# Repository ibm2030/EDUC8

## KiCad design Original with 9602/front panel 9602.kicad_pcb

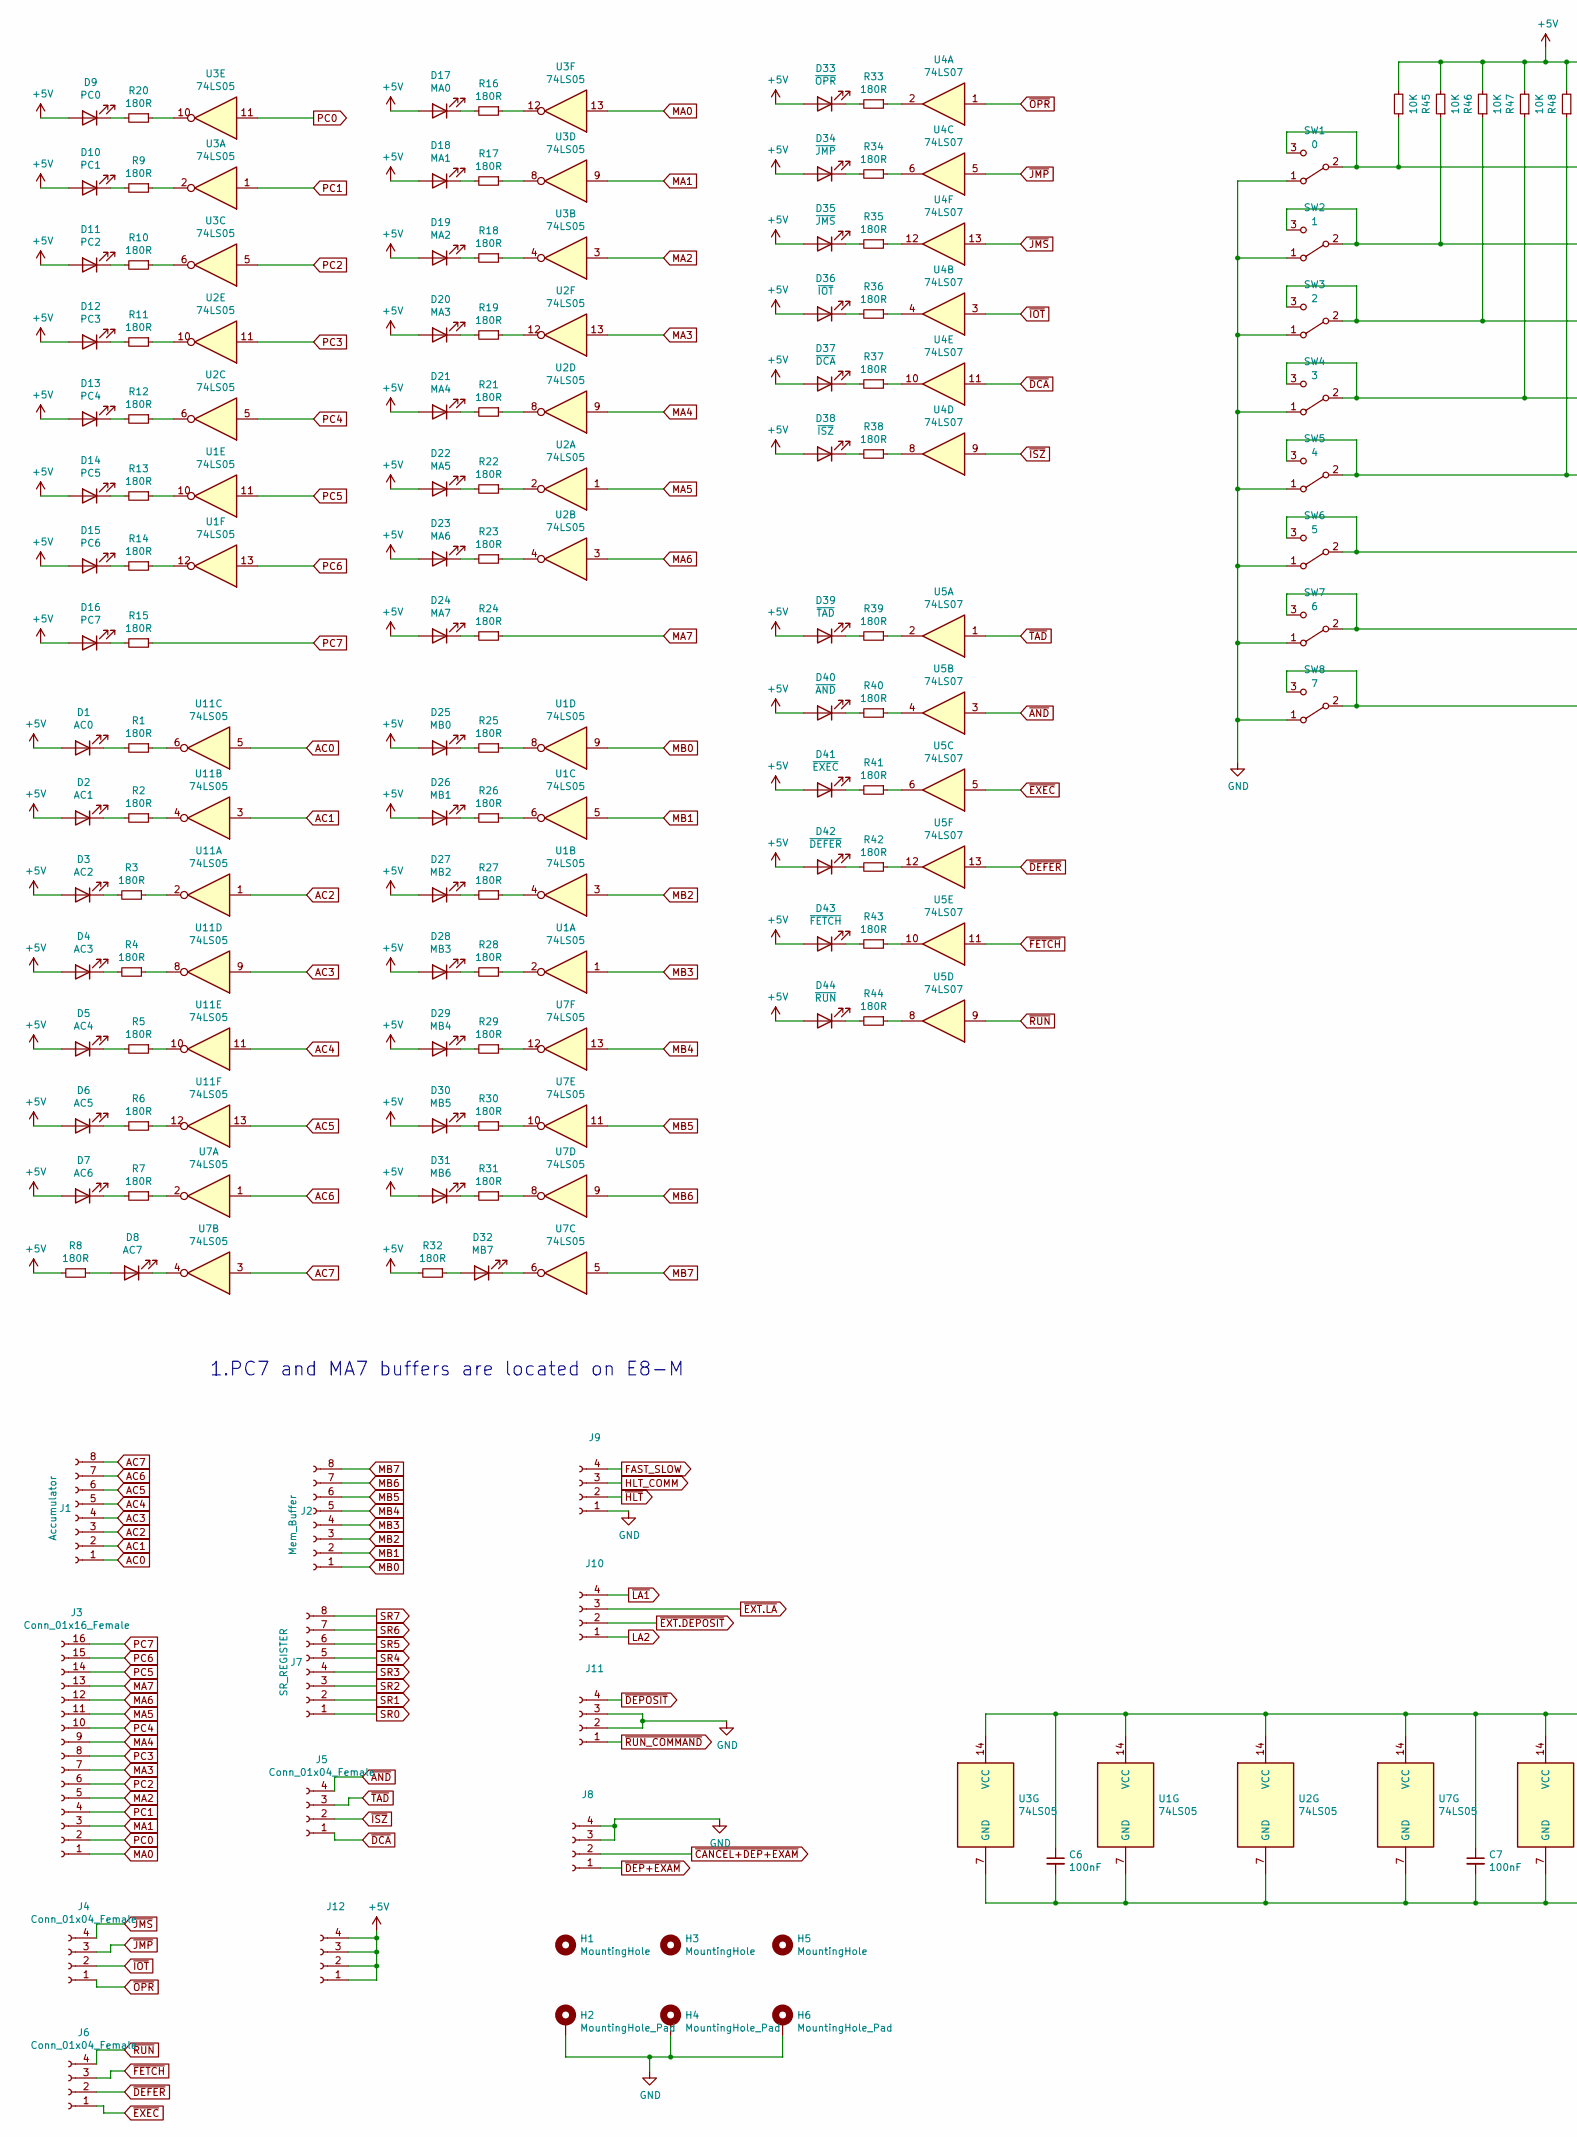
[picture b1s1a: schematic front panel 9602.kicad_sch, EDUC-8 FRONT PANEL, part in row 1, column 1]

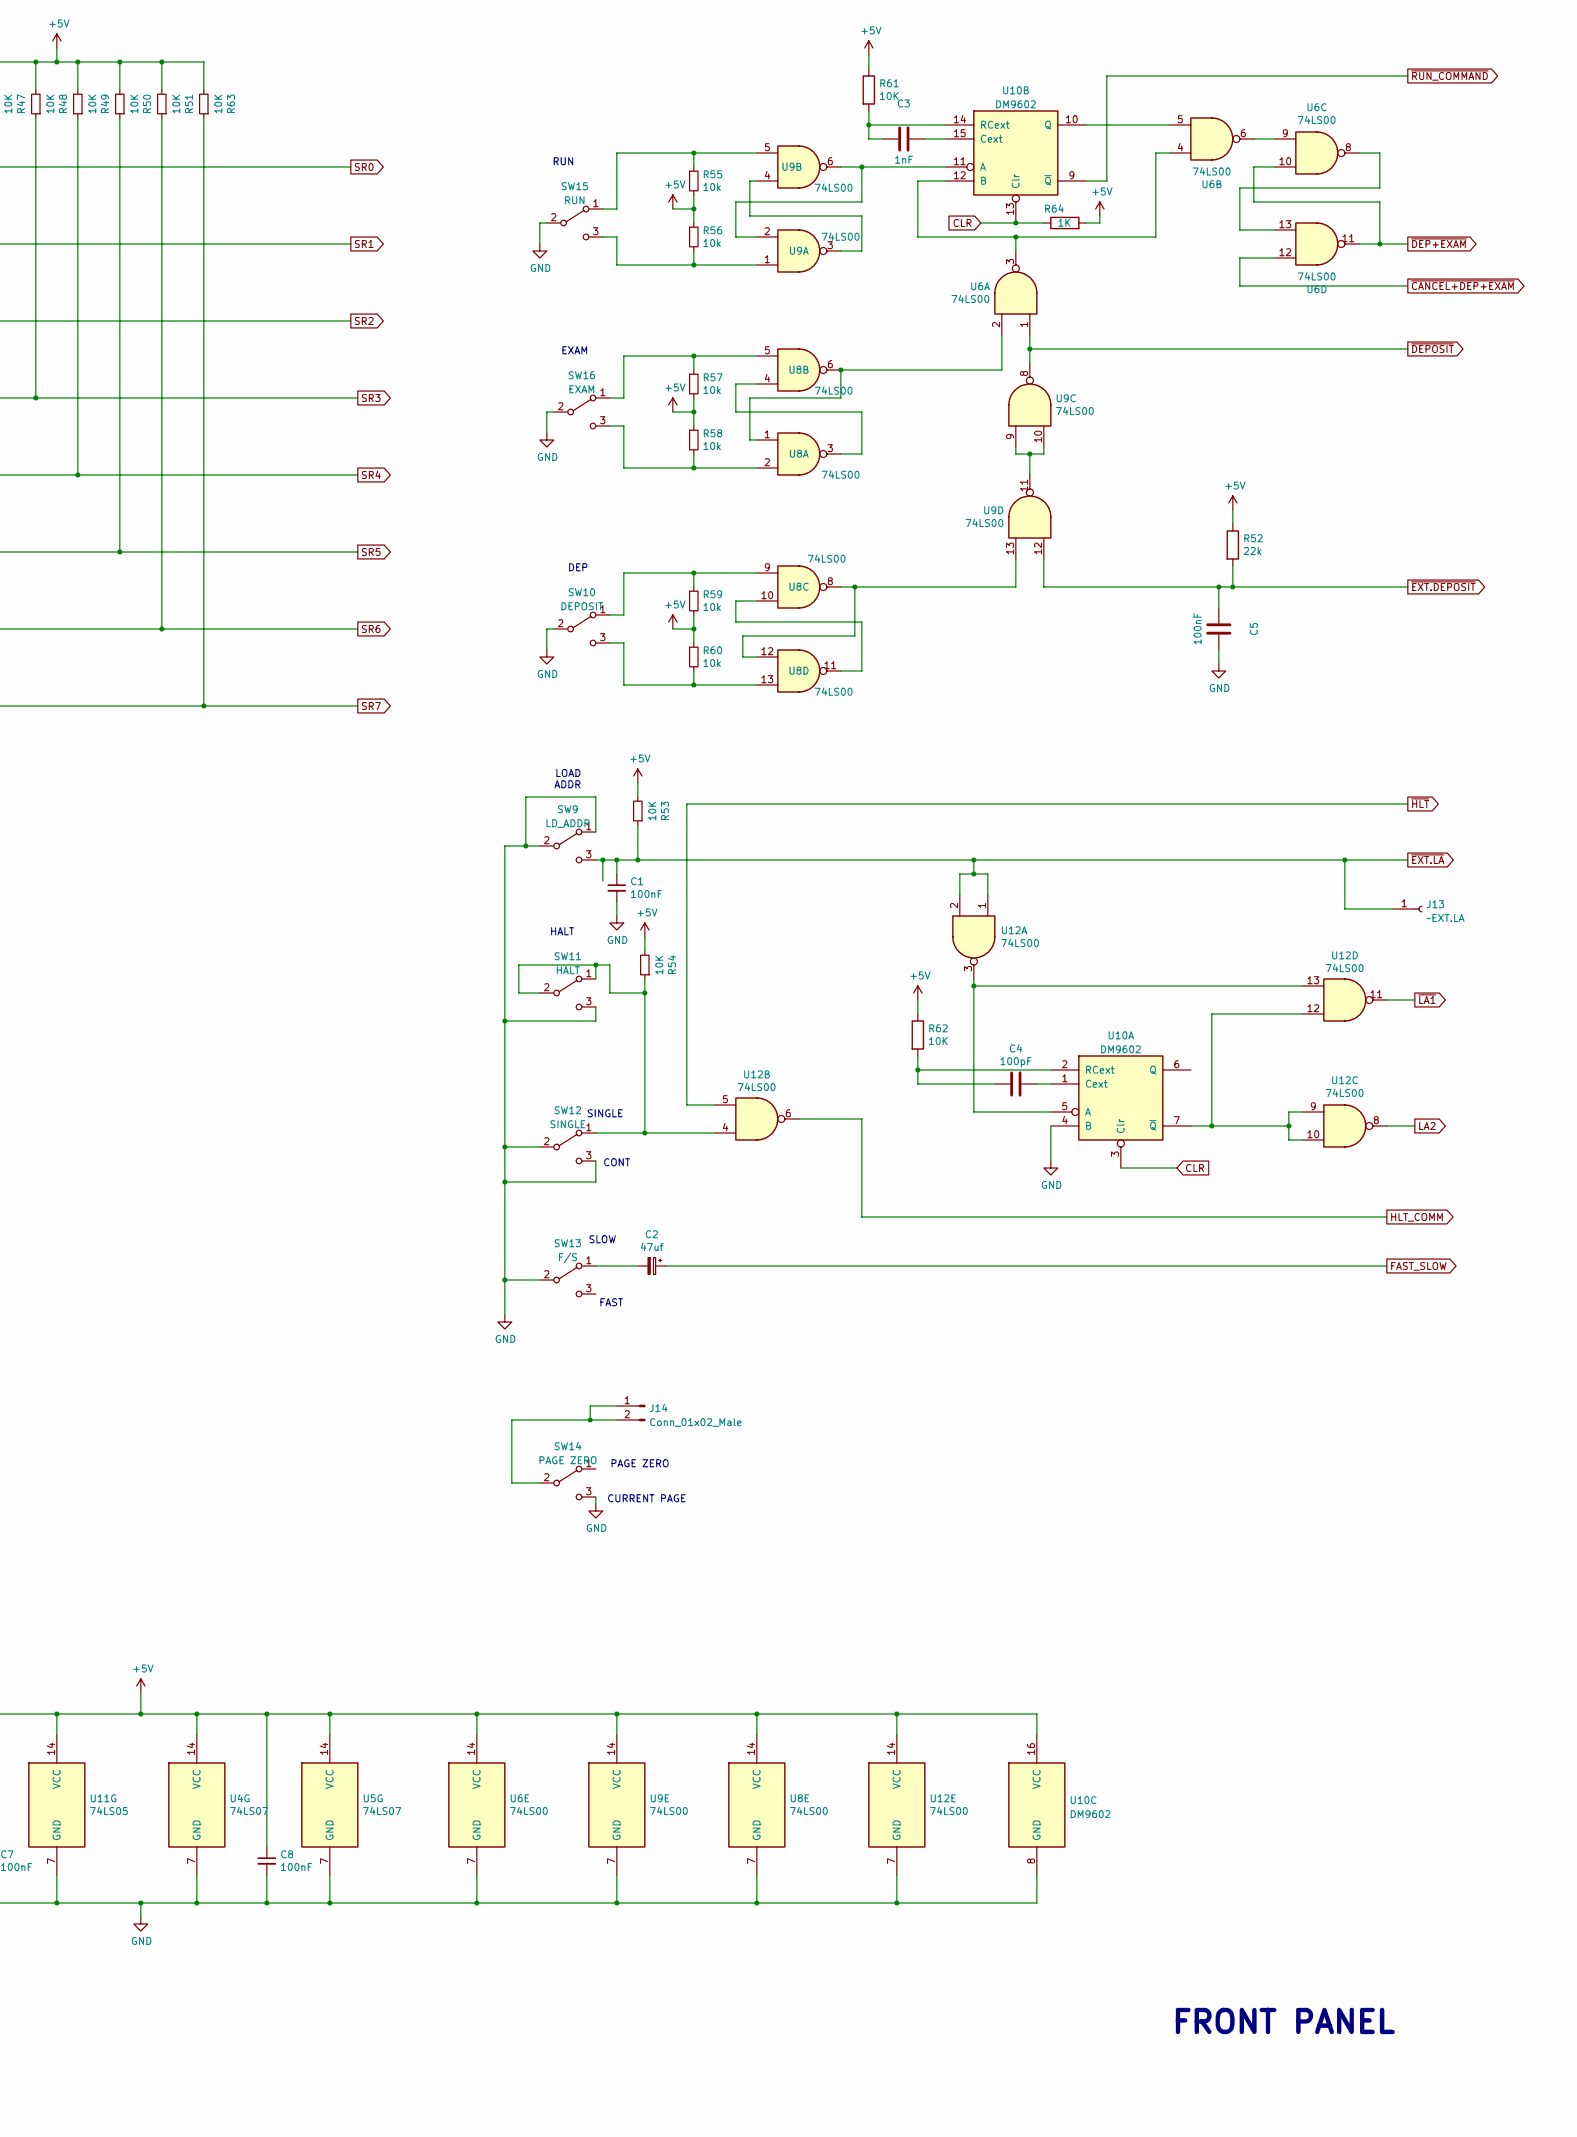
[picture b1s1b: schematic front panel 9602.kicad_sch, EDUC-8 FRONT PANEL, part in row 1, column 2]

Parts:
C1, C5: 100nF; C_Disc_D4.3mm_W1.9mm_P5.00mm
C2: 47uf; CP_Axial_L10.0mm_D6.0mm_P15.00mm_Horizontal
C3: 1nF; C_Disc_D4.3mm_W1.9mm_P5.00mm
C4: 100pF; C_Disc_D4.3mm_W1.9mm_P5.00mm
C6, C7, C8: 100nF; C_Disc_D5.0mm_W2.5mm_P5.00mm
D1: AC0; LED_D5.0mm
D2: AC1; LED_D5.0mm
D3: AC2; LED_D5.0mm
D4: AC3; LED_D5.0mm
D5: AC4; LED_D5.0mm
D6: AC5; LED_D5.0mm
D7: AC6; LED_D5.0mm
D8: AC7; LED_D5.0mm
D9: PC0; LED_D5.0mm
D10: PC1; LED_D5.0mm
D11: PC2; LED_D5.0mm
D12: PC3; LED_D5.0mm
D13: PC4; LED_D5.0mm
D14: PC5; LED_D5.0mm
D15: PC6; LED_D5.0mm
D16: PC7; LED_D5.0mm
D17: MA0; LED_D5.0mm
D18: MA1; LED_D5.0mm
D19: MA2; LED_D5.0mm
D20: MA3; LED_D5.0mm
D21: MA4; LED_D5.0mm
D22: MA5; LED_D5.0mm
D23: MA6; LED_D5.0mm
D24: MA7; LED_D5.0mm
D25: MB0; LED_D5.0mm
D26: MB1; LED_D5.0mm
D27: MB2; LED_D5.0mm
D28: MB3; LED_D5.0mm
D29: MB4; LED_D5.0mm
D30: MB5; LED_D5.0mm
D31: MB6; LED_D5.0mm
D32: MB7; LED_D5.0mm
D33: ~{OPR}; LED_D5.0mm
D34: ~{JMP}; LED_D5.0mm
D35: ~{JMS}; LED_D5.0mm
D36: ~{IOT}; LED_D5.0mm
D37: ~{DCA}; LED_D5.0mm
D38: ~{ISZ}; LED_D5.0mm
D39: ~{TAD}; LED_D5.0mm
D40: ~{AND}; LED_D5.0mm
D41: ~{EXEC}; LED_D5.0mm
D42: ~{DEFER}; LED_D5.0mm
D43: ~{FETCH}; LED_D5.0mm
D44: ~{RUN}; LED_D5.0mm
H1, H3, H5: MountingHole; MountingHole_3.2mm_M3
H2, H4, H6: MountingHole_Pad; MountingHole_3.2mm_M3_Pad_Via
J1: Accumulator; PinSocket_1x08_P2.54mm_Vertical
J2: Mem_Buffer; PinSocket_1x08_P2.54mm_Vertical
J3: Conn_01x16_Female; PinSocket_1x16_P2.54mm_Vertical
J4, J5, J6, J8, J9, J10, J11, J12: Conn_01x04_Female; PinSocket_1x04_P2.54mm_Vertical
J7: SR_REGISTER; PinSocket_1x08_P2.54mm_Vertical
J13: ~EXT.LA; PinSocket_1x01_P2.54mm_Vertical
J14: Conn_01x02_Male; JST_XH_B2B-XH-A_1x02_P2.50mm_Vertical
R1, R2, R3, R4, R5, R6, R7, R8, R9, R10, R11, R12, R13, R14, R15, R16, R17, R18, R19, R20, R21, R22, R24, R25, R26, R27, R28, R29, R30, R31, R32, R33, R34, R35, R36, R37, R38, R39, R40, R41, R42, R43, R44: 180R; R_Axial_DIN0207_L6.3mm_D2.5mm_P10.16mm_Horizontal
R23: 180R; R_Axial_DIN0207_L6.3mm_D2.5mm_P15.24mm_Horizontal
R45, R46, R47, R48, R49, R50, R51, R53, R54, R61, R62, R63: 10K; R_Axial_DIN0207_L6.3mm_D2.5mm_P10.16mm_Horizontal
R52: 22k; R_Axial_DIN0207_L6.3mm_D2.5mm_P10.16mm_Horizontal
R55, R56, R57, R58, R59, R60: 10k; R_Axial_DIN0207_L6.3mm_D2.5mm_P10.16mm_Horizontal
R64: 1K; R_Axial_DIN0207_L6.3mm_D2.5mm_P10.16mm_Horizontal
SW1: 0; SPDT_toggle_switch_wired
SW2: 1; SPDT_toggle_switch_wired
SW3: 2; SPDT_toggle_switch_wired
SW4: 3; SPDT_toggle_switch_wired
SW5: 4; SPDT_toggle_switch_wired
SW6: 5; SPDT_toggle_switch_wired
SW7: 6; SPDT_toggle_switch_wired
SW8: 7; SPDT_toggle_switch_wired
SW9: LD_ADDR; SPDT_toggle_switch_wired
SW10: DEPOSIT; SPDT_toggle_switch_wired
SW11: HALT; SPDT_toggle_switch_wired
SW12: SINGLE; SPDT_toggle_switch_wired
SW13: F/S; SPDT_toggle_switch_wired
SW14: PAGE ZERO; SPDT_toggle_switch_wired
SW15: RUN; SPDT_toggle_switch_wired
SW16: EXAM; SPDT_toggle_switch_wired
U1, U3, U7, U11: 74LS05; DIP-14_W7.62mm_LongPads
U2: 74LS05; DIP-14_W7.62mm
U4, U5: 74LS07; DIP-14_W7.62mm_LongPads
U6, U8, U9, U12: 74LS00; DIP-14_W7.62mm_LongPads
U10: DM9602; DIP-16_W7.62mm_Socket_LongPads

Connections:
+5V: C6.1, C7.1, C8.1, D1.2 (A), D2.2 (A), D3.2 (A), D4.2 (A), D5.2 (A), D6.2 (A), D7.2 (A), D9.2 (A), D10.2 (A), D11.2 (A), D12.2 (A), D13.2 (A), D14.2 (A), D15.2 (A), D16.2 (A), D17.2 (A), D18.2 (A), D19.2 (A), D20.2 (A), D21.2 (A), D22.2 (A), D23.2 (A), D24.2 (A), D25.2 (A), D26.2 (A), D27.2 (A), D28.2 (A), D29.2 (A), D30.2 (A), D31.2 (A), D33.2 (A), D34.2 (A), D35.2 (A), D36.2 (A), D37.2 (A), D38.2 (A), D39.2 (A), D40.2 (A), D41.2 (A), D42.2 (A), D43.2 (A), D44.2 (A), J12.1, J12.2, J12.3, J12.4, R8.2, R32.2, R45.2, R46.2, R47.2, R48.2, R49.2, R50.2, R51.2, R52.1, R53.2, R54.2, R55.2, R56.1, R57.2, R58.1, R59.2, R60.1, R61.1, R62.1, R63.2, R64.2, U1.14 (VCC), U2.14 (VCC), U3.14 (VCC), U4.14 (VCC), U5.14 (VCC), U6.14 (VCC), U7.14 (VCC), U8.14 (VCC), U9.14 (VCC), U10.16 (VCC), U11.14 (VCC), U12.14 (VCC)
AC0: J1.1, U11.5
AC1: J1.2, U11.3
AC2: J1.3, U11.1
AC3: J1.4, U11.9
AC4: J1.5, U11.11
AC5: J1.6, U11.13
AC6: J1.7, U7.1
AC7: J1.8, U7.3
CLR: R64.1, U10.3 (Clr), U10.13 (Clr)
FAST_SLOW: C2.1, J9.4
GND: C1.2, C5.1, C6.2, C7.2, C8.2, H2.1, H4.1, H6.1, J8.3, J8.4, J9.1, J11.2, J11.3, SW1.1 (A), SW2.1 (A), SW3.1 (A), SW4.1 (A), SW5.1 (A), SW6.1 (A), SW7.1 (A), SW8.1 (A), SW9.1 (A), SW9.2 (B), SW10.2 (B), SW11.3 (C), SW12.2 (B), SW12.3 (C), SW13.2 (B), SW14.3 (C), SW15.2 (B), SW16.2 (B), U1.7 (GND), U2.7 (GND), U3.7 (GND), U4.7 (GND), U5.7 (GND), U6.7 (GND), U7.7 (GND), U8.7 (GND), U9.7 (GND), U10.4 (B), U10.8 (GND), U11.7 (GND), U12.7 (GND)
HLT_COMM: J9.3, U12.6
LA2: J10.1, U12.8
MA0: J3.1, U3.13
MA1: J3.3, U3.9
MA2: J3.5, U3.3
MA3: J3.7, U2.13
MA4: J3.9, U2.9
MA5: J3.11, U2.1
MA6: J3.12, U2.3
MA7: J3.13, R24.1
MB0: J2.1, U1.9
MB1: J2.2, U1.5
MB2: J2.3, U1.3
MB3: J2.4, U1.1
MB4: J2.5, U7.13
MB5: J2.6, U7.11
MB6: J2.7, U7.9
MB7: J2.8, U7.5
unnamed: C3.1, U10.15 (Cext)
unnamed: C3.2, R61.2, U10.14 (RCext)
unnamed: C4.1, U10.1 (Cext)
unnamed: C4.2, R62.2, U10.2 (RCext)
unnamed: D1.1 (K), R1.2
unnamed: D2.1 (K), R2.2
unnamed: D3.1 (K), R3.2
unnamed: D4.1 (K), R4.2
unnamed: D5.1 (K), R5.2
unnamed: D6.1 (K), R6.2
unnamed: D7.1 (K), R7.2
unnamed: D8.1 (K), U7.4
unnamed: D8.2 (A), R8.1
unnamed: D9.1 (K), R20.2
unnamed: D10.1 (K), R9.2
unnamed: D11.1 (K), R10.2
unnamed: D12.1 (K), R11.2
unnamed: D13.1 (K), R12.2
unnamed: D14.1 (K), R13.2
unnamed: D15.1 (K), R14.2
unnamed: D16.1 (K), R15.2
unnamed: D17.1 (K), R16.2
unnamed: D18.1 (K), R17.2
unnamed: D19.1 (K), R18.2
unnamed: D20.1 (K), R19.2
unnamed: D21.1 (K), R21.2
unnamed: D22.1 (K), R22.2
unnamed: D23.1 (K), R23.2
unnamed: D24.1 (K), R24.2
unnamed: D25.1 (K), R25.2
unnamed: D26.1 (K), R26.2
unnamed: D27.1 (K), R27.2
unnamed: D28.1 (K), R28.2
unnamed: D29.1 (K), R29.2
unnamed: D30.1 (K), R30.2
unnamed: D31.1 (K), R31.2
unnamed: D32.1 (K), U7.6
unnamed: D32.2 (A), R32.1
unnamed: D33.1 (K), R33.2
unnamed: D34.1 (K), R34.2
unnamed: D35.1 (K), R35.2
unnamed: D36.1 (K), R36.2
unnamed: D37.1 (K), R37.2
unnamed: D38.1 (K), R38.2
unnamed: D39.1 (K), R39.2
unnamed: D40.1 (K), R40.2
unnamed: D41.1 (K), R41.2
unnamed: D42.1 (K), R42.2
unnamed: D43.1 (K), R43.2
unnamed: D44.1 (K), R44.2
unnamed: R1.1, U11.6
unnamed: R2.1, U11.4
unnamed: R3.1, U11.2
unnamed: R4.1, U11.8
unnamed: R5.1, U11.10
unnamed: R6.1, U11.12
unnamed: R7.1, U7.2
unnamed: R9.1, U3.2
unnamed: R10.1, U3.6
unnamed: R11.1, U2.10
unnamed: R12.1, U2.6
unnamed: R13.1, U1.10
unnamed: R14.1, U1.12
unnamed: R16.1, U3.12
unnamed: R17.1, U3.8
unnamed: R18.1, U3.4
unnamed: R19.1, U2.12
unnamed: R20.1, U3.10
unnamed: R21.1, U2.8
unnamed: R22.1, U2.2
unnamed: R23.1, U2.4
unnamed: R25.1, U1.8
unnamed: R26.1, U1.6
unnamed: R27.1, U1.4
unnamed: R28.1, U1.2
unnamed: R29.1, U7.12
unnamed: R30.1, U7.10
unnamed: R31.1, U7.8
unnamed: R33.1, U4.2
unnamed: R34.1, U4.6
unnamed: R35.1, U4.12
unnamed: R36.1, U4.4
unnamed: R37.1, U4.10
unnamed: R38.1, U4.8
unnamed: R39.1, U5.2
unnamed: R40.1, U5.4
unnamed: R41.1, U5.6
unnamed: R42.1, U5.12
unnamed: R43.1, U5.10
unnamed: R44.1, U5.8
unnamed: R54.1, SW11.1 (A), SW11.2 (B), SW12.1 (A), U12.4
unnamed: R55.1, SW15.1 (A), U9.5
unnamed: R56.2, SW15.3 (C), U9.1
unnamed: R57.1, SW16.1 (A), U8.5
unnamed: R58.2, SW16.3 (C), U8.2
unnamed: R59.1, SW10.1 (A), U8.9
unnamed: R60.2, SW10.3 (C), U8.13
unnamed: J14.1, J14.2, SW14.2 (B)
unnamed: U6.2, U8.1, U8.6
unnamed: U6.6, U6.9
unnamed: U6.8, U6.13
unnamed: U8.3, U8.4
unnamed: U8.10, U8.11
unnamed: U8.8, U8.12, U9.13
unnamed: U9.3, U9.4
unnamed: U9.9, U9.10, U9.11
unnamed: U10.5 (A), U12.3, U12.13
unnamed: U10.7 (~Q), U12.9, U12.10, U12.12
unnamed: U6.5, U10.10 (Q)
unnamed: U9.2, U9.6, U10.11 (A)
unnamed: U6.3, U6.4, U10.12 (B)
PC0: J3.2, U3.11
PC1: J3.4, U3.1
PC2: J3.6, U3.5
PC3: J3.8, U2.11
PC4: J3.10, U2.5
PC5: J3.14, U1.11
PC6: J3.15, U1.13
PC7: J3.16, R15.1
SR0: J7.1, R45.1, SW1.2 (B), SW1.3 (C)
SR1: J7.2, R46.1, SW2.2 (B), SW2.3 (C)
SR2: J7.3, R47.1, SW3.2 (B), SW3.3 (C)
SR3: J7.4, R48.1, SW4.2 (B), SW4.3 (C)
SR4: J7.5, R49.1, SW5.2 (B), SW5.3 (C)
SR5: J7.6, R50.1, SW6.2 (B), SW6.3 (C)
SR6: J7.7, R51.1, SW7.2 (B), SW7.3 (C)
SR7: J7.8, R63.1, SW8.2 (B), SW8.3 (C)
~AND: J5.4, U5.3
~CANCEL+DEP+EXAM: J8.2, U6.12
~DCA: J5.1, U4.11
~DEFER: J6.2, U5.13
~DEP+EXAM: J8.1, U6.10, U6.11
~DEPOSIT: J11.4, U6.1, U9.8
~EXEC: J6.1, U5.5
~EXT.DEPOSIT: C5.2, J10.2, R52.2, U9.12
~EXT.LA: C1.1, J10.3, J13.1, R53.1, SW9.3 (C), U12.1, U12.2
~FETCH: J6.3, U5.11
~HLT: J9.2, U12.5
~IOT: J4.2, U4.3
~ISZ: J5.2, U4.9
~JMP: J4.3, U4.5
~JMS: J4.4, U4.13
~LA1: J10.4, U12.11
~OPR: J4.1, U4.1
~RUN_COMMAND: J11.1, U10.9 (~Q)
~RUN: J6.4, U5.9
~TAD: J5.3, U5.1

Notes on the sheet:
SINGLE
PAGE ZERO
1.PC7 and MA7 buffers are located on E8-M
EXAM
HALT
CONT
FAST
FRONT PANEL
RUN
SLOW
CURRENT PAGE
LOAD ADDR
DEP

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
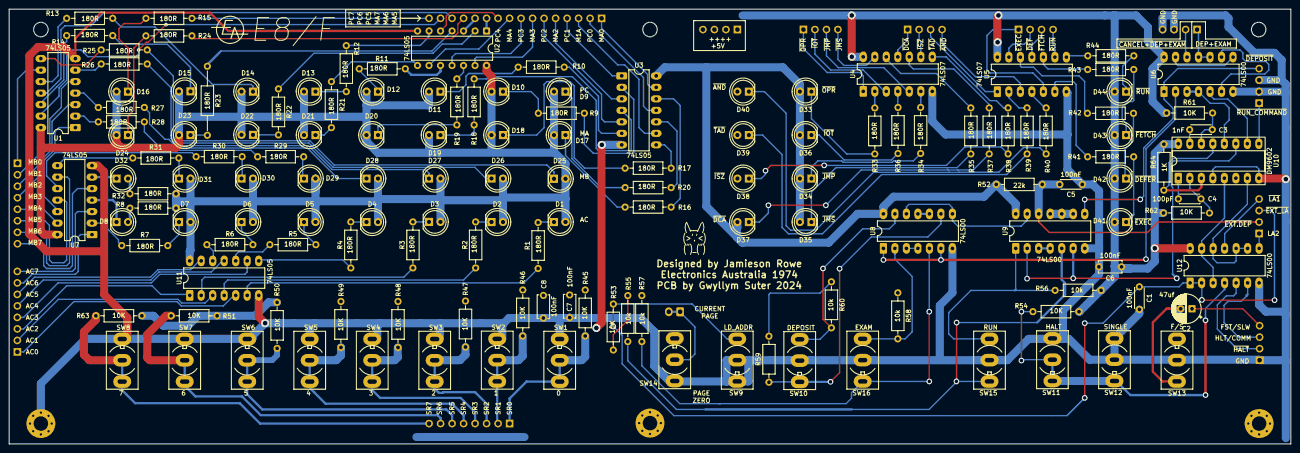
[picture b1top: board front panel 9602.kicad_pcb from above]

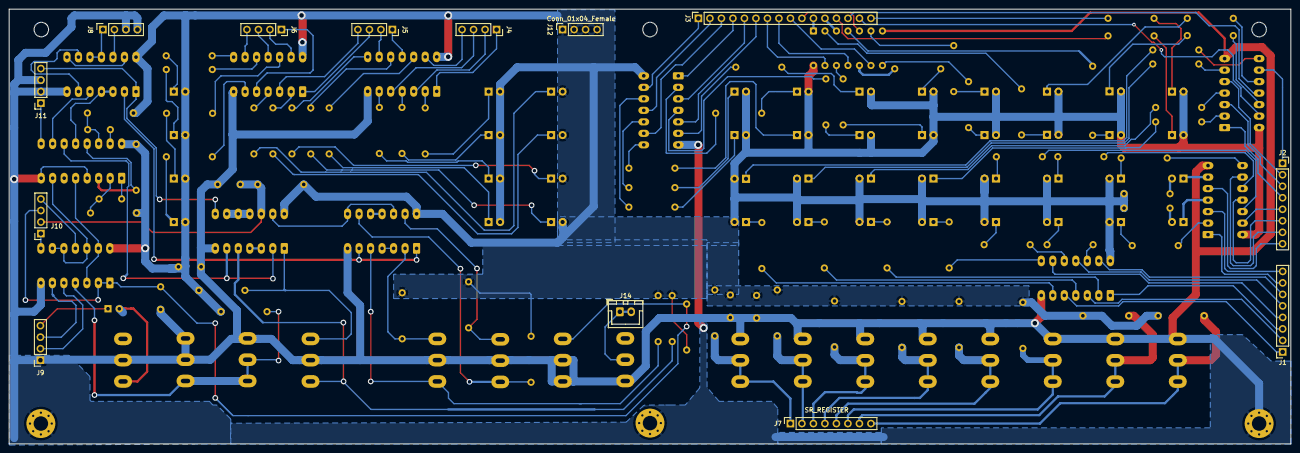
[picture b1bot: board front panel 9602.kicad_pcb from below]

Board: 2 copper layers, 283.0 x 96.0 mm, 163 parts (13 on the bottom side), 178 nets.

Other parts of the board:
HE: MountingHole; MountingHole_3.2mm_M3

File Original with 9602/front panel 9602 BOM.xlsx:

# | Reference | Qty | Value | Footprint | DNP
1 | C1, C5 | 2 | 100nF | Capacitor_THT:C_Disc_D4.3mm_W1.9mm_P5.00mm
2 | C2 | 1 | 47uf | Capacitor_THT:CP_Axial_L10.0mm_D6.0mm_P15.00mm_Horizontal
3 | C3 | 1 | 1nF | Capacitor_THT:C_Disc_D4.3mm_W1.9mm_P5.00mm
4 | C4 | 1 | 100pF | Capacitor_THT:C_Disc_D4.3mm_W1.9mm_P5.00mm
5 | C6, C7, C8 | 3 | 100nF | Capacitor_THT:C_Disc_D5.0mm_W2.5mm_P5.00mm
6 | D1 | 1 | AC0 | LED_THT:LED_D5.0mm
7 | D2 | 1 | AC1 | LED_THT:LED_D5.0mm
8 | D3 | 1 | AC2 | LED_THT:LED_D5.0mm
9 | D4 | 1 | AC3 | LED_THT:LED_D5.0mm
10 | D5 | 1 | AC4 | LED_THT:LED_D5.0mm
11 | D6 | 1 | AC5 | LED_THT:LED_D5.0mm
12 | D7 | 1 | AC6 | LED_THT:LED_D5.0mm
13 | D8 | 1 | AC7 | LED_THT:LED_D5.0mm
14 | D9 | 1 | PC0 | LED_THT:LED_D5.0mm
15 | D10 | 1 | PC1 | LED_THT:LED_D5.0mm
16 | D11 | 1 | PC2 | LED_THT:LED_D5.0mm
17 | D12 | 1 | PC3 | LED_THT:LED_D5.0mm
18 | D13 | 1 | PC4 | LED_THT:LED_D5.0mm
19 | D14 | 1 | PC5 | LED_THT:LED_D5.0mm
20 | D15 | 1 | PC6 | LED_THT:LED_D5.0mm
21 | D16 | 1 | PC7 | LED_THT:LED_D5.0mm
22 | D17 | 1 | MA0 | LED_THT:LED_D5.0mm
23 | D18 | 1 | MA1 | LED_THT:LED_D5.0mm
24 | D19 | 1 | MA2 | LED_THT:LED_D5.0mm
25 | D20 | 1 | MA3 | LED_THT:LED_D5.0mm
26 | D21 | 1 | MA4 | LED_THT:LED_D5.0mm
27 | D22 | 1 | MA5 | LED_THT:LED_D5.0mm
28 | D23 | 1 | MA6 | LED_THT:LED_D5.0mm
29 | D24 | 1 | MA7 | LED_THT:LED_D5.0mm
30 | D25 | 1 | MB0 | LED_THT:LED_D5.0mm
31 | D26 | 1 | MB1 | LED_THT:LED_D5.0mm
32 | D27 | 1 | MB2 | LED_THT:LED_D5.0mm
33 | D28 | 1 | MB3 | LED_THT:LED_D5.0mm
34 | D29 | 1 | MB4 | LED_THT:LED_D5.0mm
35 | D30 | 1 | MB5 | LED_THT:LED_D5.0mm
36 | D31 | 1 | MB6 | LED_THT:LED_D5.0mm
37 | D32 | 1 | MB7 | LED_THT:LED_D5.0mm
38 | D33 | 1 | ~{OPR} | LED_THT:LED_D5.0mm
39 | D34 | 1 | ~{JMP} | LED_THT:LED_D5.0mm
40 | D35 | 1 | ~{JMS} | LED_THT:LED_D5.0mm
41 | D36 | 1 | ~{IOT} | LED_THT:LED_D5.0mm
42 | D37 | 1 | ~{DCA} | LED_THT:LED_D5.0mm
43 | D38 | 1 | ~{ISZ} | LED_THT:LED_D5.0mm
44 | D39 | 1 | ~{TAD} | LED_THT:LED_D5.0mm
45 | D40 | 1 | ~{AND} | LED_THT:LED_D5.0mm
46 | D41 | 1 | ~{EXEC} | LED_THT:LED_D5.0mm
47 | D42 | 1 | ~{DEFER} | LED_THT:LED_D5.0mm
48 | D43 | 1 | ~{FETCH} | LED_THT:LED_D5.0mm
49 | D44 | 1 | ~{RUN} | LED_THT:LED_D5.0mm
50 | H1, H3, H5 | 3 | MountingHole | MountingHole:MountingHole_3.2mm_M3
51 | H2, H4, H6 | 3 | MountingHole_Pad | MountingHole:MountingHole_3.2mm_M3_Pad_Via
52 | J1 | 1 | Accumulator | Connector_PinSocket_2.54mm:PinSocket_1x08_P2.54mm_Vertical
53 | J2 | 1 | Mem_Buffer | Connector_PinSocket_2.54mm:PinSocket_1x08_P2.54mm_Vertical
54 | J3 | 1 | Conn_01x16_Female | Connector_PinSocket_2.54mm:PinSocket_1x16_P2.54mm_Vertical
55 | J4, J5, J6, J8, J9, J10, J11, J12 | 8 | Conn_01x04_Female | Connector_PinSocket_2.54mm:PinSocket_1x04_P2.54mm_Vertical
56 | J7 | 1 | SR_REGISTER | Connector_PinSocket_2.54mm:PinSocket_1x08_P2.54mm_Vertical
57 | J13 | 1 | ~EXT.LA | Connector_PinSocket_2.54mm:PinSocket_1x01_P2.54mm_Vertical
58 | J14 | 1 | Conn_01x02_Male | Connector_JST:JST_XH_B2B-XH-A_1x02_P2.50mm_Vertical
59 | R1, R2, R3, R4, R5, R6, R7, R8, R9, R10, R11, R12, R13, R14, R15, R16, R17, R18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 | 43 | 180R | Resistor_THT:R_Axial_DIN0207_L6.3mm_D2.5mm_P10.16mm_Horizontal
60 | R23 | 1 | 180R | Resistor_THT:R_Axial_DIN0207_L6.3mm_D2.5mm_P15.24mm_Horizontal
61 | R45, R46, R47, R48, R49, R50, R51, R53, R54, R61, R62, R63 | 12 | 10K | Resistor_THT:R_Axial_DIN0207_L6.3mm_D2.5mm_P10.16mm_Horizontal
62 | R52 | 1 | 22k | Resistor_THT:R_Axial_DIN0207_L6.3mm_D2.5mm_P10.16mm_Horizontal
63 | R55, R56, R57, R58, R59, R60 | 6 | 10k | Resistor_THT:R_Axial_DIN0207_L6.3mm_D2.5mm_P10.16mm_Horizontal
64 | R64 | 1 | 1K | Resistor_THT:R_Axial_DIN0207_L6.3mm_D2.5mm_P10.16mm_Horizontal
65 | SW1 | 1 | 0 | EDUC-8:SPDT_toggle_switch_wired
66 | SW2 | 1 | 1 | EDUC-8:SPDT_toggle_switch_wired
67 | SW3 | 1 | 2 | EDUC-8:SPDT_toggle_switch_wired
68 | SW4 | 1 | 3 | EDUC-8:SPDT_toggle_switch_wired
69 | SW5 | 1 | 4 | EDUC-8:SPDT_toggle_switch_wired
70 | SW6 | 1 | 5 | EDUC-8:SPDT_toggle_switch_wired
71 | SW7 | 1 | 6 | EDUC-8:SPDT_toggle_switch_wired
72 | SW8 | 1 | 7 | EDUC-8:SPDT_toggle_switch_wired
73 | SW9 | 1 | LD_ADDR | EDUC-8:SPDT_toggle_switch_wired
74 | SW10 | 1 | DEPOSIT | EDUC-8:SPDT_toggle_switch_wired
75 | SW11 | 1 | HALT | EDUC-8:SPDT_toggle_switch_wired
76 | SW12 | 1 | SINGLE | EDUC-8:SPDT_toggle_switch_wired
77 | SW13 | 1 | F/S | EDUC-8:SPDT_toggle_switch_wired
78 | SW14 | 1 | PAGE ZERO | EDUC-8:SPDT_toggle_switch_wired
79 | SW15 | 1 | RUN | EDUC-8:SPDT_toggle_switch_wired
80 | SW16 | 1 | EXAM | EDUC-8:SPDT_toggle_switch_wired
81 | U1, U3, U7, U11 | 4 | 74LS05 | Package_DIP:DIP-14_W7.62mm_LongPads
82 | U2 | 1 | 74LS05 | Package_DIP:DIP-14_W7.62mm
83 | U4, U5 | 2 | 74LS07 | Package_DIP:DIP-14_W7.62mm_LongPads
84 | U6, U8, U9, U12 | 4 | 74LS00 | Package_DIP:DIP-14_W7.62mm_LongPads
85 | U10 | 1 | DM9602 | Package_DIP:DIP-16_W7.62mm_Socket_LongPads

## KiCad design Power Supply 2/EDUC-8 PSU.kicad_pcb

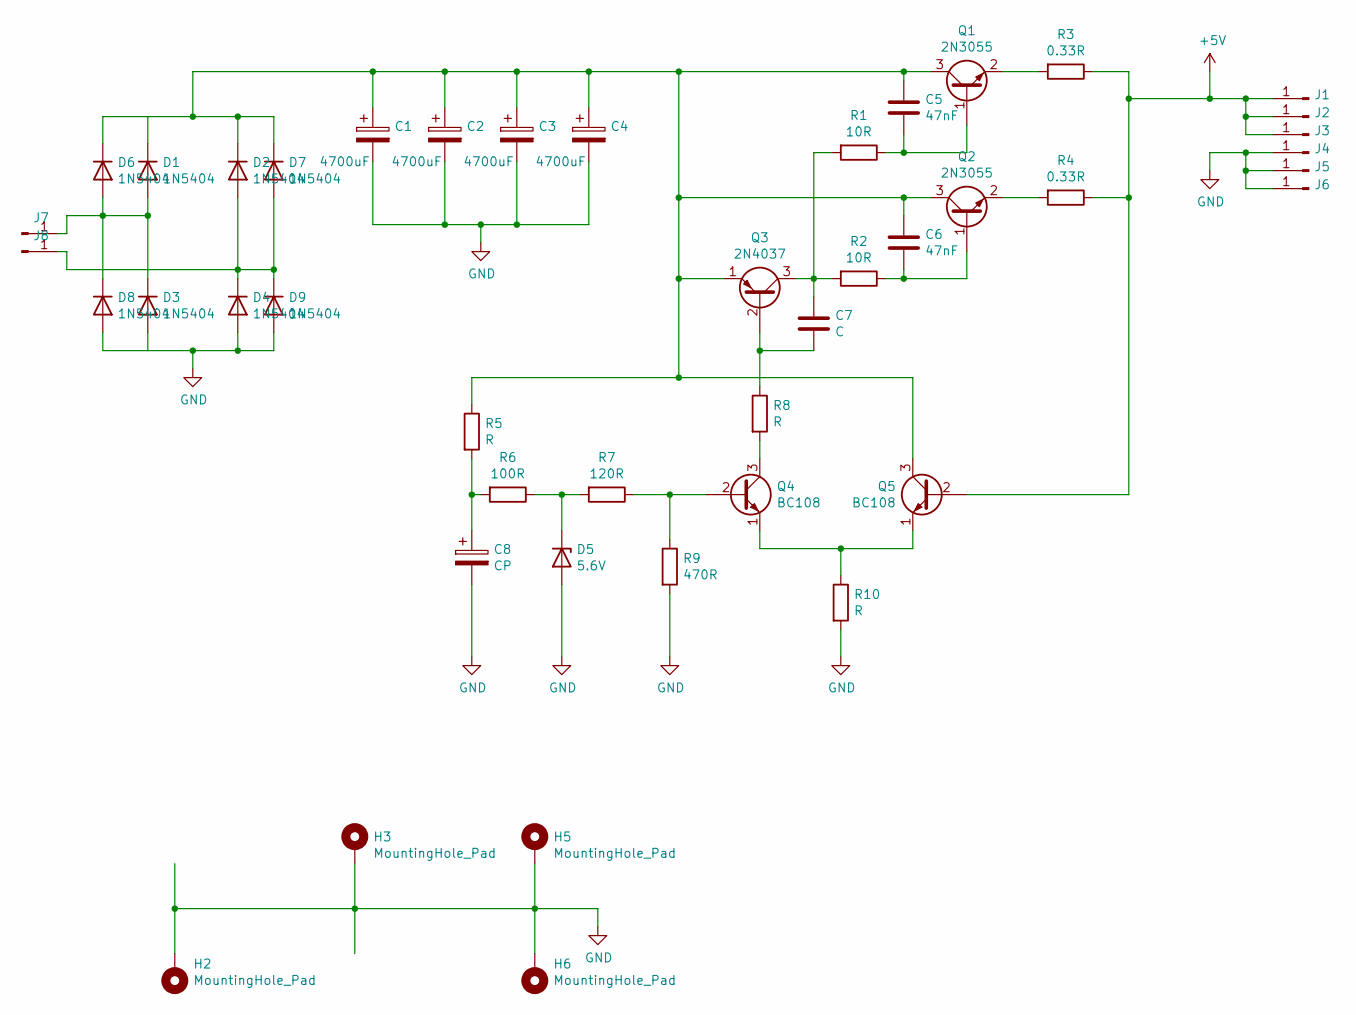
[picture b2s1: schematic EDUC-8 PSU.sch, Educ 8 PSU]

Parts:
C1, C2, C3, C4: 4700uF; CP_Radial_D25.0mm_P10.00mm_SnapIn
C5, C6: 47nF; C_Rect_L7.2mm_W3.5mm_P5.00mm_FKS2_FKP2_MKS2_MKP2
C7: C; C_Rect_L7.0mm_W6.0mm_P5.00mm
C8: CP; CP_Radial_D12.5mm_P5.00mm
D1, D2, D3, D4, D6, D7, D8, D9: 1N5404; D_DO-201AD_P15.24mm_Horizontal
D5: 5.6V; D_DO-41_SOD81_P10.16mm_Horizontal
H2, H3, H5, H6: MountingHole_Pad; MountingHole_4.3mm_M4_Pad_Via
J1, J2, J3, J4, J5, J6, J7, J8: Conn_01x01_Male; QC_Terminal_PCB_W6.3mm_P5mm_
Q1, Q2: 2N3055; TO-3
Q3: 2N4037; TO-39-3
Q4, Q5: BC108; TO-18-3
R1, R2: 10R; R_Axial_DIN0411_L9.9mm_D3.6mm_P15.24mm_Horizontal
R3, R4: 0.33R; R_Axial_Power_L25.0mm_W9.0mm_P30.48mm
R5, R8, R10: R; R_Axial_DIN0411_L9.9mm_D3.6mm_P15.24mm_Horizontal
R6: 100R; R_Axial_DIN0411_L9.9mm_D3.6mm_P15.24mm_Horizontal
R7: 120R; R_Axial_DIN0411_L9.9mm_D3.6mm_P15.24mm_Horizontal
R9: 470R; R_Axial_DIN0411_L9.9mm_D3.6mm_P15.24mm_Horizontal

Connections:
+5V: J1.1, J2.1, J3.1, Q5.2 (B), R3.1, R4.1; also elsewhere on the board
GND: C1.2, C2.2, C3.2, C4.2, C8.2, D3.2 (A), D4.2 (A), D5.2 (A), D8.2 (A), D9.2 (A), H2.1, H3.1, H5.1, H6.1, J4.1, J5.1, J6.1, R9.2, R10.2; also elsewhere on the board
unnamed: C1.1, C2.1, C3.1, C4.1, C5.1, C6.1, D1.1 (K), D2.1 (K), D6.1 (K), D7.1 (K), Q1.3 (C), Q2.3 (C), Q3.1 (E), Q5.3 (C), R5.1
unnamed: C5.2, Q1.1 (B), R1.1
unnamed: C6.2, Q2.1 (B), R2.1
unnamed: C7.1, Q3.3 (C), R1.2, R2.2
unnamed: C7.2, Q3.2 (B), R8.1
unnamed: C8.1, R5.2, R6.2
unnamed: D1.2 (A), D3.1 (K), D6.2 (A), D8.1 (K), J7.1
unnamed: D2.2 (A), D4.1 (K), D7.2 (A), D9.1 (K), J8.1
unnamed: D5.1 (K), R6.1, R7.2
unnamed: Q1.2 (E), R3.2
unnamed: Q2.2 (E), R4.2
unnamed: Q4.1 (E), Q5.1 (E), R10.1
unnamed: Q4.2 (B), R7.1, R9.1
unnamed: Q4.3 (C), R8.2

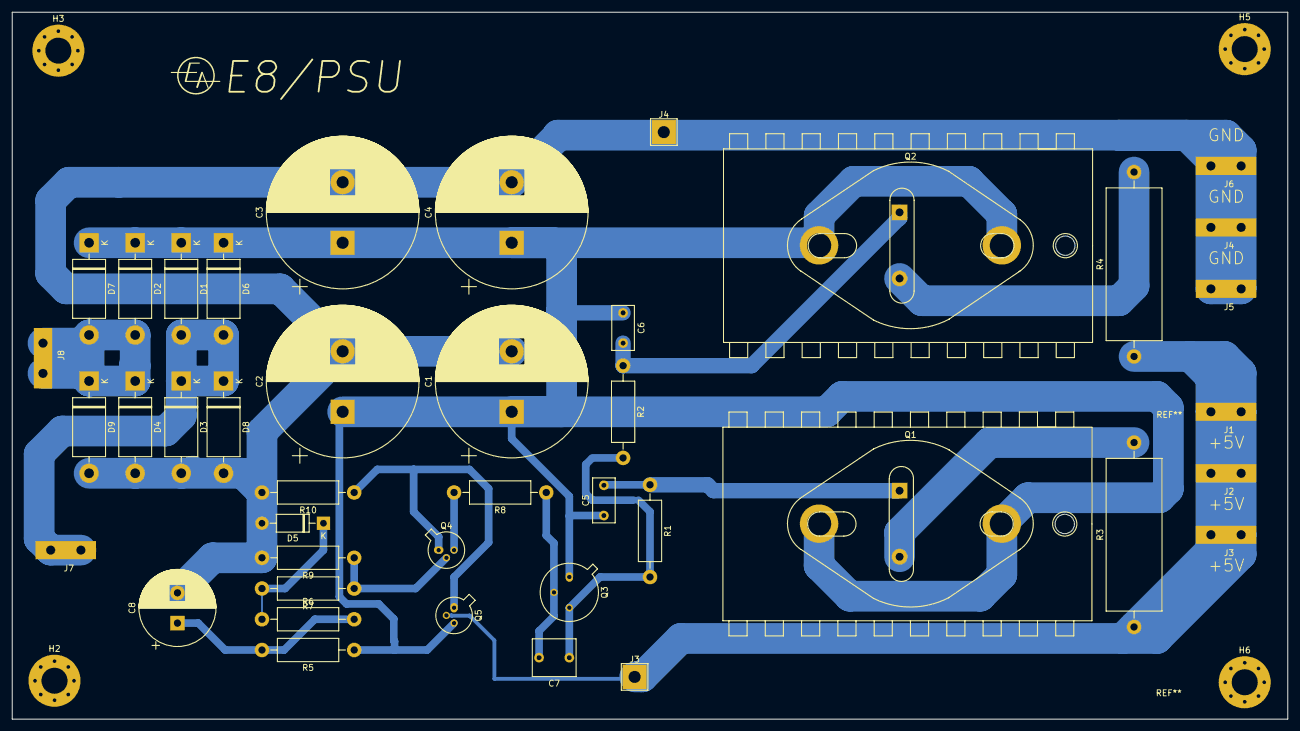
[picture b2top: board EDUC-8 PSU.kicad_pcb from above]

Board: 2 copper layers, 210.8 x 116.8 mm, 46 parts (0 on the bottom side), 16 nets.

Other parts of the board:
J3#2, J4#2: Conn_01x01; TestPoint_THTPad_4.0x4.0mm_Drill2.0mm

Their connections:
+5V: J3#2.1; also elsewhere on the board
GND: J4#2.1; also elsewhere on the board
